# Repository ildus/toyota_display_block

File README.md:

# atmega8 based controller for Toyota's headunit display block

I wanted to use panel from Toyota, so I created special controller that can work with it and send all its events
to another block using serial interface. I used Panasonic datasheet (you can find it in the root) to understand how 
the panel works. Controller works on 5V, but requires 10V input for backlight (if you need it).

## Panel's look:

## Schematic:

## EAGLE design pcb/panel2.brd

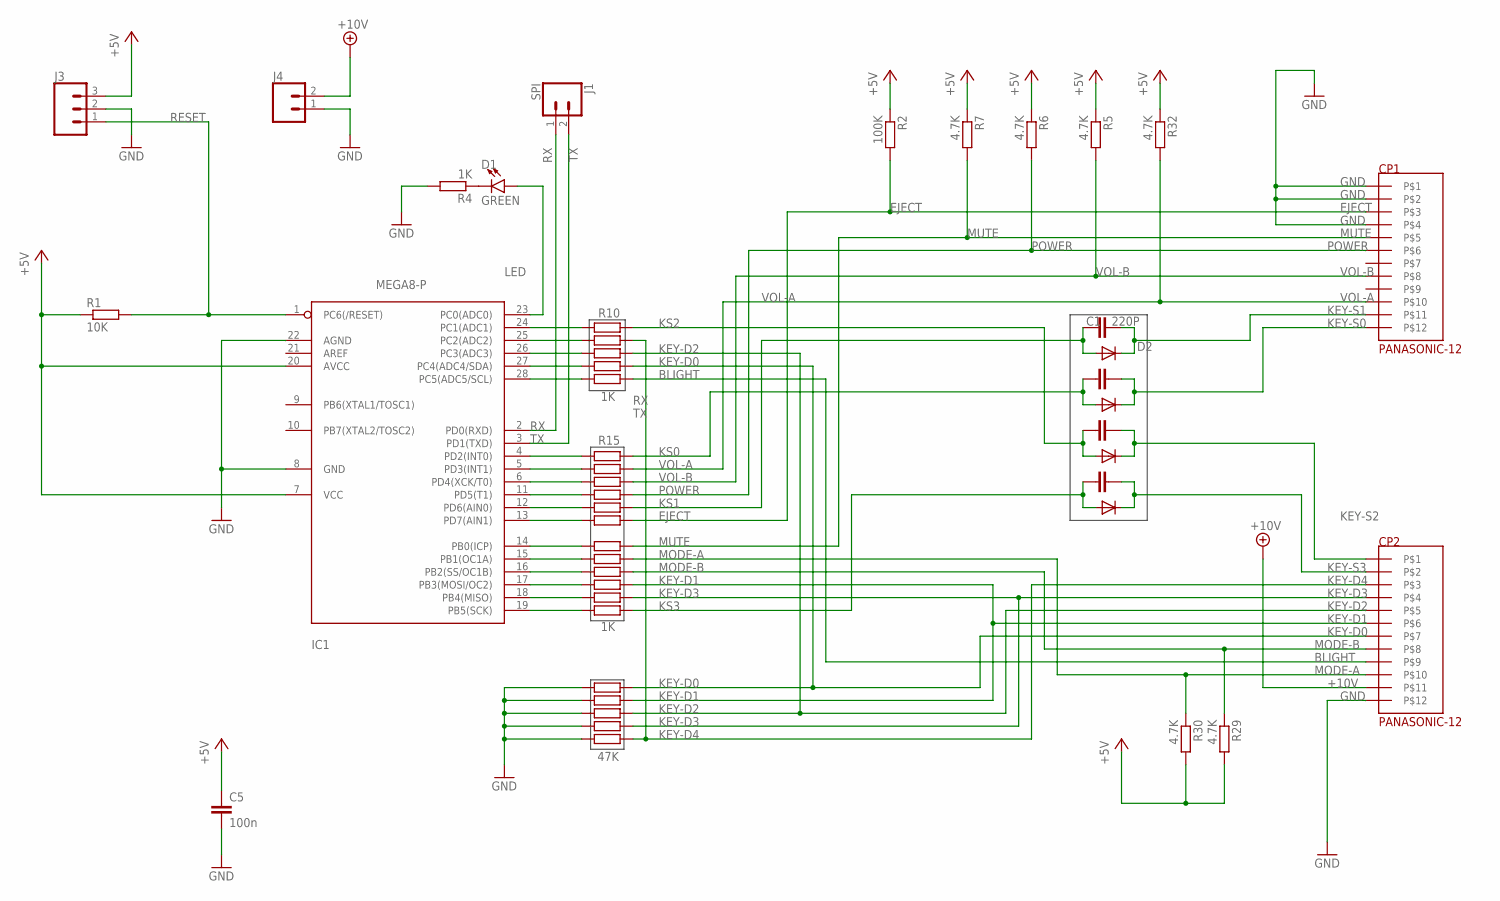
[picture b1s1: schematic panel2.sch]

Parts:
C1, C2, C3, C4: 220P; C0805
C5: 100n; C0805
CP1, CP2: PANASONIC-12
D1: GREEN; LED-1206
D2, D3, D4, D5: 1N4148DO35-10; DO35-10
IC1: MEGA8-P; DIL28-3
J1: SPI; 1X02_LONGPADS
J3: CONN_03LONGPADS; 1X03_LONGPADS
J4: CONN_02LOCK_LONGPADS; 1X02_LOCK_LONGPADS
R1: 10K; M0805
R2: 100K; M0805
R3, R24, R25, R28, R34: 47K; 0207/10
R4, R8, R9, R10, R11, R12, R13, R14, R15, R16, R17, R18, R19, R20, R21, R22, R23, R31: 1K; M0805
R5, R6, R7, R29, R30: 4.7K; M0805
R32: 4.7K; 0207/10

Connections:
+5V: C5.1, IC1.7 (VCC), IC1.20 (AVCC), J3.3, R1.1, R2.1, R5.1, R6.1, R7.1, R29.2, R30.2, R32.1
+10V: CP2.P11, J4.2
BLIGHT: CP2.P9, R14.2
EJECT: CP1.P3, R2.2, R23.2
GND: C5.2, CP1.P1, CP1.P2, CP1.P4, CP2.P12, IC1.8 (GND), IC1.22 (AGND), J3.2, J4.1, R3.2, R4.2, R24.2, R25.2, R28.2, R34.2
KEY-D0: CP2.P7, R13.2, R24.1
KEY-D1: CP2.P6, R18.2, R25.1
KEY-D2: CP2.P5, R12.2, R28.1
KEY-D3: CP2.P4, R21.2, R34.1
KEY-D4: CP2.P3, R3.1, R11.2
KEY-S0: C2.2, CP1.P12, D3.C
KEY-S1: C1.2, CP1.P11, D2.C
KEY-S2: C3.2, CP2.P1, D4.C
KEY-S3: C4.2, CP2.P2, D5.C
KS0: C2.1, D3.A, R15.2
KS1: C1.1, D2.A, R22.2
KS2: C3.1, D4.A, R10.2
KS3: C4.1, D5.A, R31.2
LED: D1.A, IC1.23 (PC0(ADC0))
MODE-A: CP2.P10, R20.2, R30.1
MODE-B: CP2.P8, R17.2, R29.1
MUTE: CP1.P5, R7.2, R19.2
unnamed: D1.C, R4.1
unnamed: IC1.4 (PD2(INT0)), R15.1
unnamed: IC1.24 (PC1(ADC1)), R10.1
unnamed: IC1.25 (PC2(ADC2)), R11.1
unnamed: IC1.26 (PC3(ADC3)), R12.1
unnamed: IC1.27 (PC4(ADC4/SDA)), R13.1
unnamed: IC1.28 (PC5(ADC5/SCL)), R14.1
unnamed: IC1.5 (PD3(INT1)), R16.1
unnamed: IC1.6 (PD4(XCK/T0)), R8.1
unnamed: IC1.11 (PD5(T1)), R9.1
unnamed: IC1.19 (PB5(SCK)), R31.1
unnamed: IC1.18 (PB4(MISO)), R21.1
unnamed: IC1.17 (PB3(MOSI/OC2)), R18.1
unnamed: IC1.16 (PB2(SS/OC1B)), R17.1
unnamed: IC1.15 (PB1(OC1A)), R20.1
unnamed: IC1.14 (PB0(ICP)), R19.1
unnamed: IC1.12 (PD6(AIN0)), R22.1
unnamed: IC1.13 (PD7(AIN1)), R23.1
POWER: CP1.P6, R6.2, R9.2
RESET: IC1.1 (PC6(/RESET)), J3.1, R1.2
RX: IC1.2 (PD0(RXD)), J1.1
TX: IC1.3 (PD1(TXD)), J1.2
VOL-A: CP1.P10, R16.2, R32.2
VOL-B: CP1.P8, R5.2, R8.2

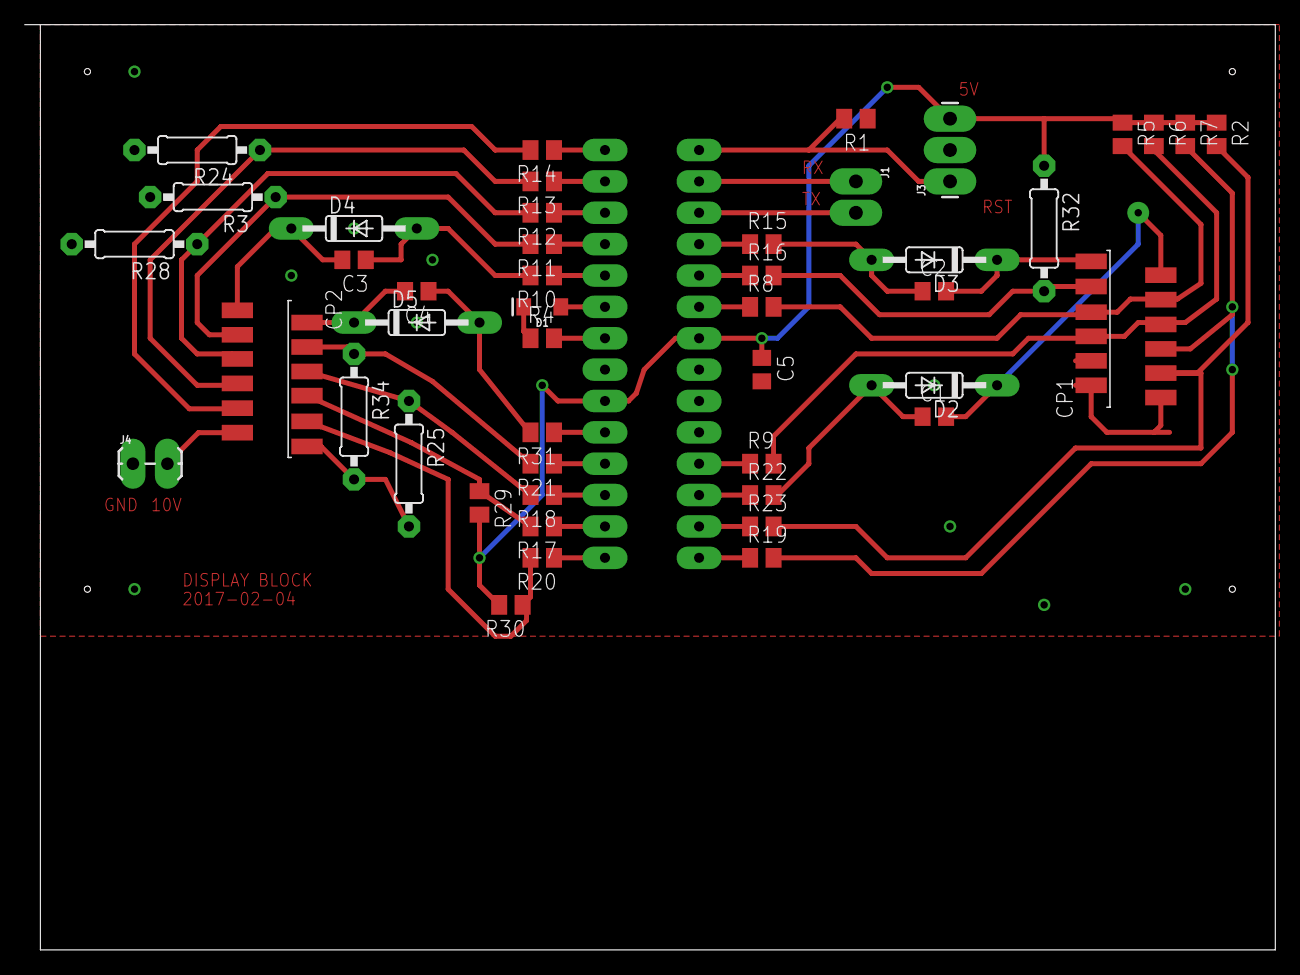
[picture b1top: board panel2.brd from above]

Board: 2 copper layers, 101.3 x 74.9 mm, 47 parts (1 on the bottom side), 46 nets.

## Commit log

2017-02-10 Initial
2017-02-10 Add bouncing and prevent double clicks
2017-02-10 Split processing and buttons checking
2017-03-11 Add eagle files
2017-03-11 Add datasheet

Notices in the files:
parts and their libraries:
SparkFun-Connectors: Licensing: Creative Commons ShareAlike 4.0 International - https://creativecommons.org/licenses/by-sa/4.0
